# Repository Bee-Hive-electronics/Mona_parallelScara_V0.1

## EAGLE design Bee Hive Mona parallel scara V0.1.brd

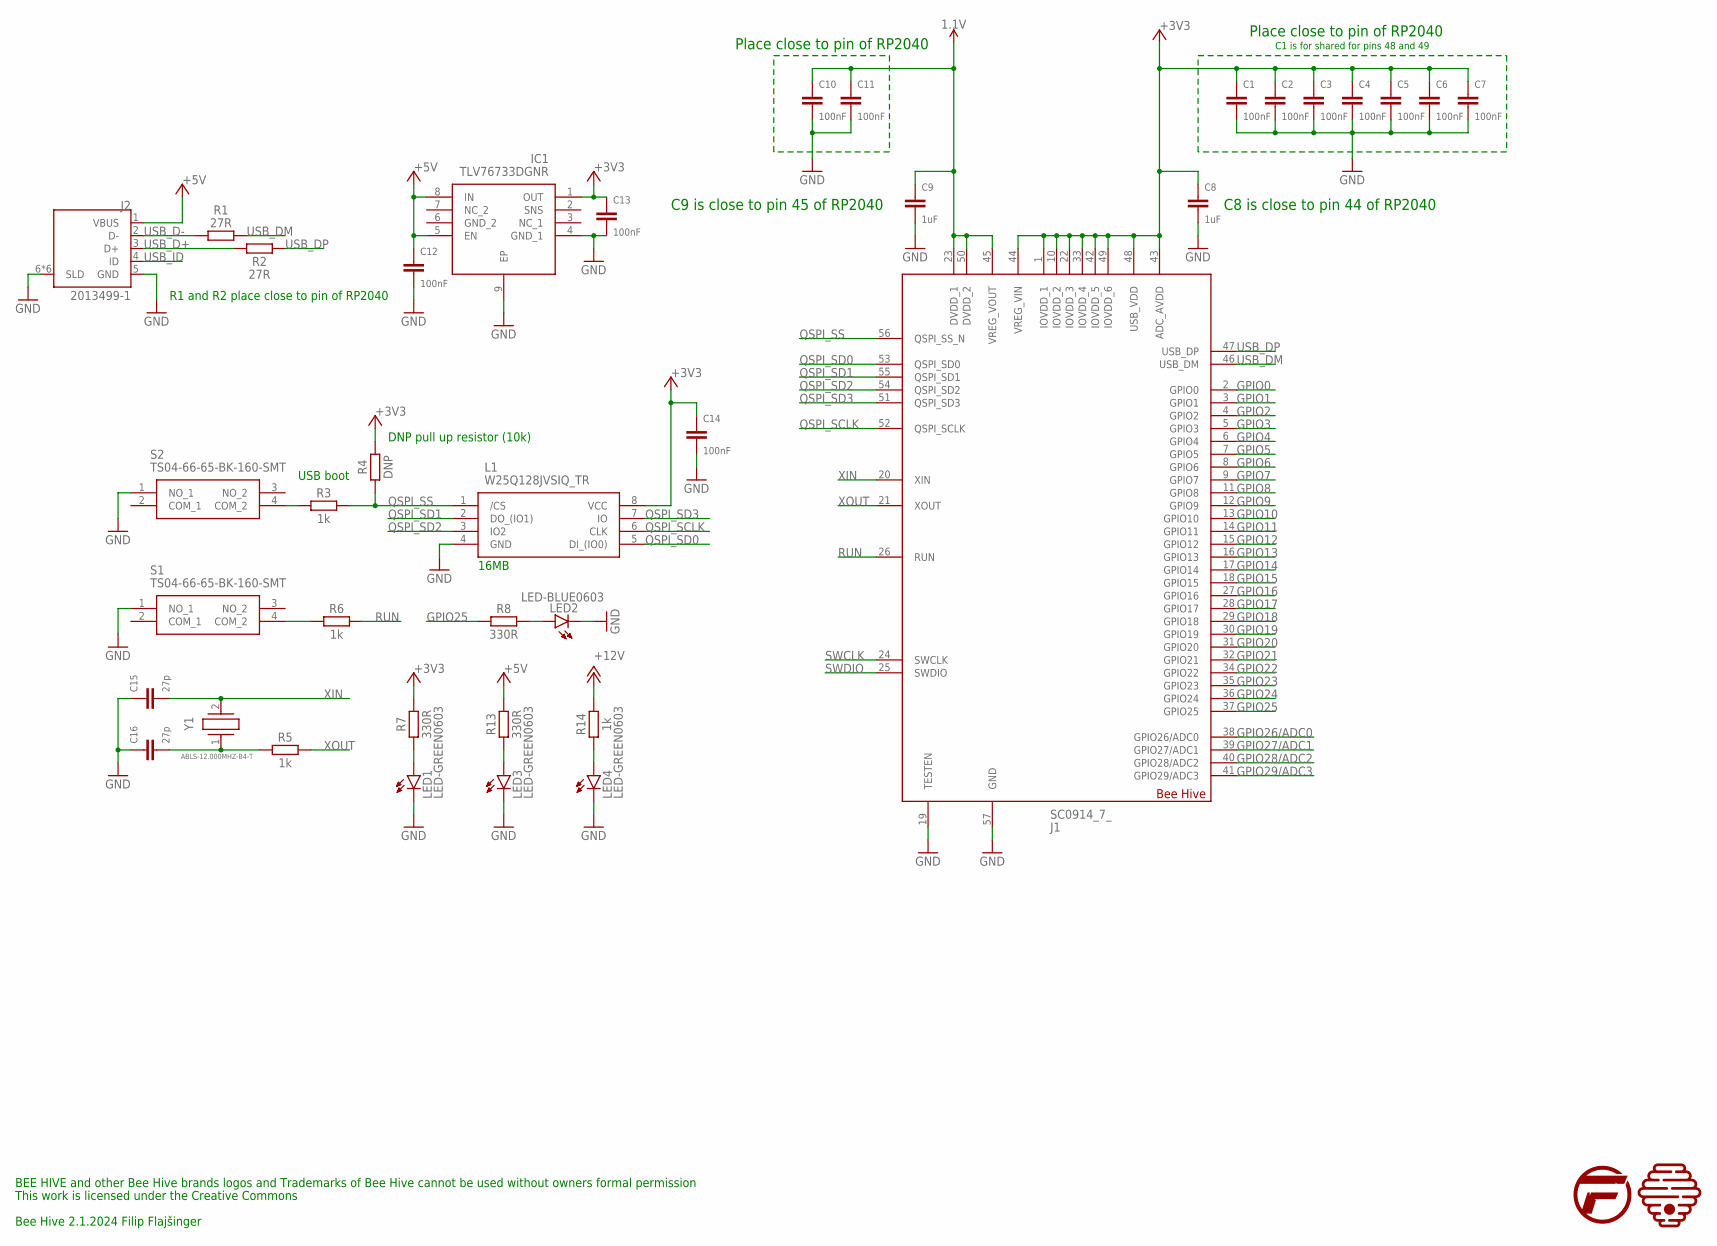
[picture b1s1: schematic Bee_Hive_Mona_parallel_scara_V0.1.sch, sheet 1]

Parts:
C1, C2, C3, C4, C5, C6, C7, C10, C11, C12, C13, C14: 100nF; CAPC1608X85
C8, C9: 1uF; CAPC1608X85
C15, C16: 27p; CAPC1608X85
IC1: TLV76733DGNR; SOP65P490X110-9N
J1: SC0914_7_; QFN40P700X700X90-57N
J2: 2013499-1; TE_2013499-1
L1: W25Q128JVSIQ_TR; SOIC127P780X195-8N
LED1, LED3, LED4: LED-GREEN0603; 0603-GREEN
LED2: LED-BLUE0603; 0603-BLUE
R1, R2: 27R; RESC1608X60
R3, R5, R6, R14: 1k; RESC1608X60
R4: DNP; RESC1608X60
R7, R8, R13: 330R; RESC1608X60
S1, S2: TS04-66-65-BK-160-SMT; TS046665BK160SMT
Y1: ABLS-12.000MHZ-B4-T; ABLS

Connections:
1.1V: C9.1, C10.1, C11.1, J1.23 (DVDD_1), J1.45 (VREG_VOUT), J1.50 (DVDD_2)
+3V3: C1.1, C2.1, C3.1, C4.1, C5.1, C6.1, C7.1, C8.1, C13.1, C14.1, IC1.1 (OUT), J1.1 (IOVDD_1), J1.10 (IOVDD_2), J1.22 (IOVDD_3), J1.33 (IOVDD_4), J1.42 (IOVDD_5), J1.43 (ADC_AVDD), J1.44 (VREG_VIN), J1.48 (USB_VDD), J1.49 (IOVDD_6), L1.8 (VCC), R4.2, R7.2; also elsewhere on the board
+5V: C12.1, IC1.5 (EN), IC1.8 (IN), J2.1 (VBUS), R13.2; also elsewhere on the board
+12V: R14.2; also elsewhere on the board
GND: C1.2, C2.2, C3.2, C4.2, C5.2, C6.2, C7.2, C8.2, C9.2, C10.2, C11.2, C12.2, C13.2, C14.2, C15.1, C16.1, IC1.4 (GND_1), IC1.9 (EP), J1.19 (TESTEN), J1.57 (GND), J2.5 (GND), J2.6 (SLD), J2.7 (SLD), J2.8 (SLD), J2.9 (SLD), J2.10 (SLD), J2.11 (SLD), L1.4 (GND), LED1.C, LED2.C, LED3.C, LED4.C, S1.1 (NO_1), S2.1 (NO_1); also elsewhere on the board
GPIO0: J1.2 (GPIO0); also elsewhere on the board
GPIO1: J1.3 (GPIO1); also elsewhere on the board
GPIO2: J1.4 (GPIO2); also elsewhere on the board
GPIO3: J1.5 (GPIO3); also elsewhere on the board
GPIO4: J1.6 (GPIO4); also elsewhere on the board
GPIO5: J1.7 (GPIO5); also elsewhere on the board
GPIO6: J1.8 (GPIO6); also elsewhere on the board
GPIO7: J1.9 (GPIO7); also elsewhere on the board
GPIO8: J1.11 (GPIO8); also elsewhere on the board
GPIO9: J1.12 (GPIO9); also elsewhere on the board
GPIO10: J1.13 (GPIO10); also elsewhere on the board
GPIO11: J1.14 (GPIO11); also elsewhere on the board
GPIO12: J1.15 (GPIO12); also elsewhere on the board
GPIO13: J1.16 (GPIO13); also elsewhere on the board
GPIO14: J1.17 (GPIO14); also elsewhere on the board
GPIO15: J1.18 (GPIO15); also elsewhere on the board
GPIO16: J1.27 (GPIO16); also elsewhere on the board
GPIO17: J1.28 (GPIO17); also elsewhere on the board
GPIO18: J1.29 (GPIO18); also elsewhere on the board
GPIO19: J1.30 (GPIO19); also elsewhere on the board
GPIO20: J1.31 (GPIO20); also elsewhere on the board
GPIO21: J1.32 (GPIO21); also elsewhere on the board
GPIO22: J1.34 (GPIO22); also elsewhere on the board
GPIO23: J1.35 (GPIO23); also elsewhere on the board
GPIO24: J1.36 (GPIO24); also elsewhere on the board
GPIO25: J1.37 (GPIO25), R8.2; also elsewhere on the board
GPIO26/ADC0: J1.38 (GPIO26/ADC0); also elsewhere on the board
GPIO27/ADC1: J1.39 (GPIO27/ADC1); also elsewhere on the board
GPIO28/ADC2: J1.40 (GPIO28/ADC2); also elsewhere on the board
GPIO29/ADC3: J1.41 (GPIO29/ADC3); also elsewhere on the board
unnamed: R3.1, S2.4 (COM_2)
unnamed: R6.1, S1.4 (COM_2)
unnamed: C16.2, R5.1, Y1.1
unnamed: LED2.A, R8.1
unnamed: LED1.A, R7.1
unnamed: LED3.A, R13.1
unnamed: LED4.A, R14.1
QSPI_SCLK: J1.52 (QSPI_SCLK), L1.6 (CLK)
QSPI_SD0: J1.53 (QSPI_SD0), L1.5 (DI_(IO0))
QSPI_SD1: J1.55 (QSPI_SD1), L1.2 (DO_(IO1))
QSPI_SD2: J1.54 (QSPI_SD2), L1.3 (IO2)
QSPI_SD3: J1.51 (QSPI_SD3), L1.7 (IO)
QSPI_SS: J1.56 (QSPI_SS_N), L1.1 (/CS), R3.2, R4.1
RUN: J1.26 (RUN), R6.2
SWCLK: J1.24 (SWCLK)
SWDIO: J1.25 (SWDIO)
USB_D+: J2.3 (D+), R2.1
USB_D-: J2.2 (D-), R1.1
USB_DM: J1.46 (USB_DM), R1.2
USB_DP: J1.47 (USB_DP), R2.2
USB_ID: J2.4 (ID)
XIN: C15.2, J1.20 (XIN), Y1.2
XOUT: J1.21 (XOUT), R5.2

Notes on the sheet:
C8 is close to pin 44 of RP2040
Place close to pin of RP2040
C9 is close to pin 45 of RP2040
C1 is for shared for pins 48 and 49
R1 and R2 place close to pin of RP2040
USB boot
DNP pull up resistor (10k)
16MB
This work is licensed under the Creative Commons
BEE HIVE and other Bee Hive brands logos and Trademarks of Bee Hive cannot be used without owners formal permission
Bee Hive 2.1.2024 Filip Flajšinger

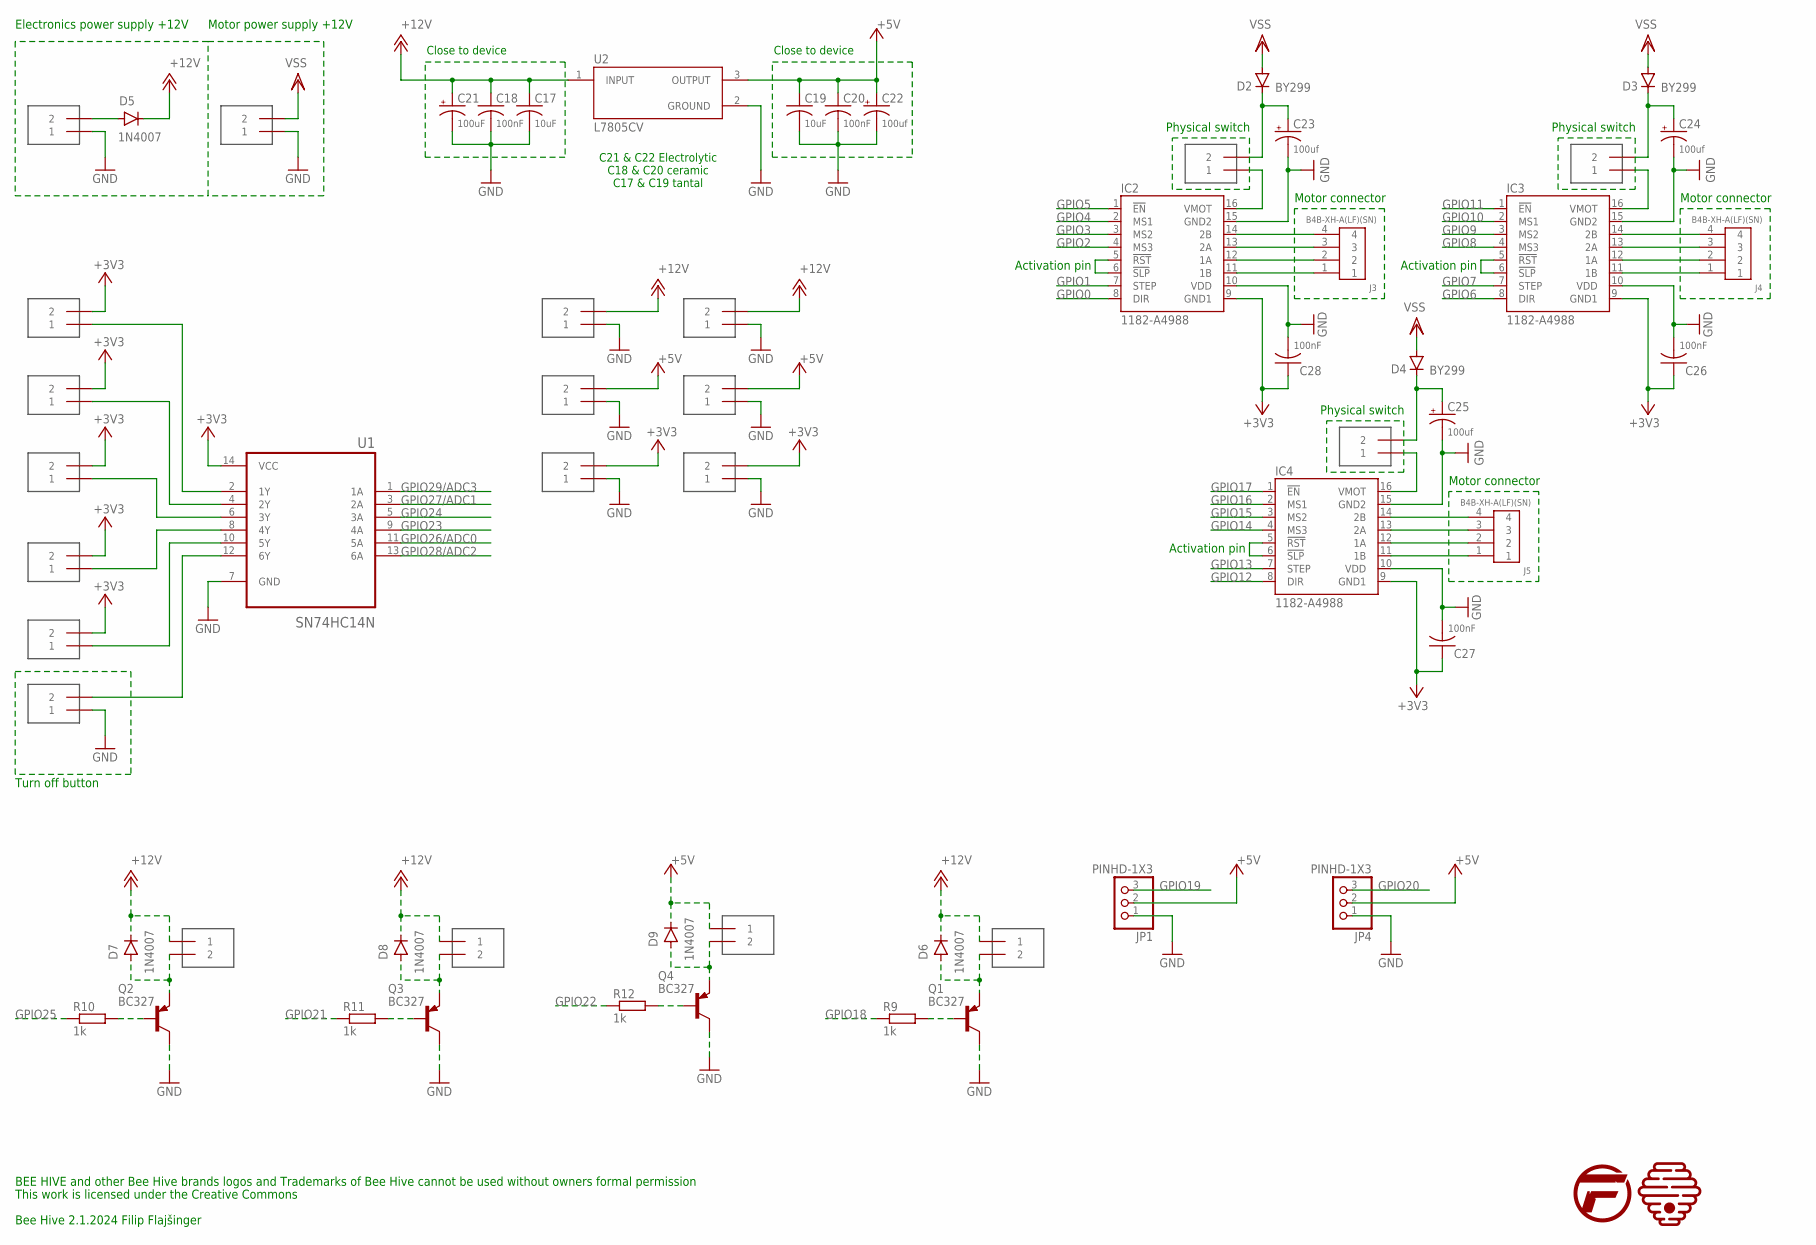
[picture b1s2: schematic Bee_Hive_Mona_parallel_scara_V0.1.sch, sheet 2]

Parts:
C17, C19: 10uF; C025-024X044
C18, C20, C26, C27, C28: 100nF; C025-024X044
C21: 100uF; E1,8-4
C22, C23, C24, C25: 100uf; E1,8-4
D2, D3, D4: BY299; DO15-12
D5, D6, D7, D8, D9: 1N4007; DO-41
IC2, IC3, IC4: 1182-A4988; A4988
J3, J4, J5: B4B-XH-A(LF)(SN)
JP1, JP4: PINHD-1X3; 1X03
Q1, Q2, Q3, Q4: BC327; TO92
R9, R10, R11, R12: 1k; 0204/7
U1: SN74HC14N; DIP794W45P254L1969H508Q14
U2: L7805CV; TO255P1040X460X1968-3
U$1, U$2, U$3, U$4, U$5, U$6, U$7, U$8, U$9, U$10, U$11, U$12, U$15, U$16, U$17, U$18, U$19, U$20, U$21, U$22, U$23: TERMINAL_2P; KF301-2P

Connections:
+3V3: C26.1, C27.1, C28.1, IC2.9 (GND1), IC3.9 (GND1), IC4.9 (GND1), U1.14 (VCC), U$12.2, U$17.2, U$18.2, U$19.2, U$20.2, U$21.2, U$23.2; also elsewhere on the board
+5V: C19.1, C20.1, C22.+, D9.C, JP1.2, JP4.2, U2.3 (OUTPUT), U$9.1, U$11.2, U$16.2; also elsewhere on the board
+12V: C17.1, C18.1, C21.+, D5.C, D6.C, D7.C, D8.C, U2.1 (INPUT), U$6.1, U$7.1, U$8.1, U$10.2, U$15.2; also elsewhere on the board
GND: C17.2, C18.2, C19.2, C20.2, C21.-, C22.-, C23.-, C24.-, C25.-, C26.2, C27.2, C28.2, IC2.10 (VDD), IC2.15 (GND2), IC3.10 (VDD), IC3.15 (GND2), IC4.10 (VDD), IC4.15 (GND2), JP1.1, JP4.1, Q1.3 (C), Q2.3 (C), Q3.3 (C), Q4.3 (C), U1.7 (GND), U2.2 (GROUND), U$4.1, U$5.1, U$10.1, U$11.1, U$12.1, U$15.1, U$16.1, U$17.1, U$22.1; also elsewhere on the board
GPIO0: IC2.8 (DIR); also elsewhere on the board
GPIO1: IC2.7 (STEP); also elsewhere on the board
GPIO2: IC2.4 (MS3); also elsewhere on the board
GPIO3: IC2.3 (MS2); also elsewhere on the board
GPIO4: IC2.2 (MS1); also elsewhere on the board
GPIO5: IC2.1 (!EN); also elsewhere on the board
GPIO6: IC3.8 (DIR); also elsewhere on the board
GPIO7: IC3.7 (STEP); also elsewhere on the board
GPIO8: IC3.4 (MS3); also elsewhere on the board
GPIO9: IC3.3 (MS2); also elsewhere on the board
GPIO10: IC3.2 (MS1); also elsewhere on the board
GPIO11: IC3.1 (!EN); also elsewhere on the board
GPIO12: IC4.8 (DIR); also elsewhere on the board
GPIO13: IC4.7 (STEP); also elsewhere on the board
GPIO14: IC4.4 (MS3); also elsewhere on the board
GPIO15: IC4.3 (MS2); also elsewhere on the board
GPIO16: IC4.2 (MS1); also elsewhere on the board
GPIO17: IC4.1 (!EN); also elsewhere on the board
GPIO18: R9.1; also elsewhere on the board
GPIO19: JP1.3; also elsewhere on the board
GPIO20: JP4.3; also elsewhere on the board
GPIO21: R11.1; also elsewhere on the board
GPIO22: R12.1; also elsewhere on the board
GPIO23: U1.9 (4A); also elsewhere on the board
GPIO24: U1.5 (3A); also elsewhere on the board
GPIO25: R10.1; also elsewhere on the board
GPIO26/ADC0: U1.11 (5A); also elsewhere on the board
GPIO27/ADC1: U1.3 (2A); also elsewhere on the board
GPIO28/ADC2: U1.13 (6A); also elsewhere on the board
GPIO29/ADC3: U1.1 (1A); also elsewhere on the board
unnamed: D5.A, U$4.2
unnamed: IC2.11 (1B), J3.1
unnamed: IC2.12 (1A), J3.2
unnamed: IC2.13 (2A), J3.3
unnamed: IC2.14 (2B), J3.4
unnamed: IC2.5 (!RST), IC2.6 (!SLP)
unnamed: IC2.16 (VMOT), U$1.1
unnamed: IC3.16 (VMOT), U$2.1
unnamed: IC4.16 (VMOT), U$3.1
unnamed: IC3.11 (1B), J4.1
unnamed: IC3.12 (1A), J4.2
unnamed: IC3.13 (2A), J4.3
unnamed: IC3.14 (2B), J4.4
unnamed: IC3.5 (!RST), IC3.6 (!SLP)
unnamed: C23.+, D2.C, U$1.2
unnamed: C24.+, D3.C, U$2.2
unnamed: C25.+, D4.C, U$3.2
unnamed: IC4.11 (1B), J5.1
unnamed: IC4.12 (1A), J5.2
unnamed: IC4.13 (2A), J5.3
unnamed: IC4.14 (2B), J5.4
unnamed: IC4.5 (!RST), IC4.6 (!SLP)
unnamed: D6.A, Q1.1 (E), U$6.2
unnamed: Q1.2 (B), R9.2
unnamed: D7.A, Q2.1 (E), U$7.2
unnamed: Q2.2 (B), R10.2
unnamed: D8.A, Q3.1 (E), U$8.2
unnamed: Q3.2 (B), R11.2
unnamed: D9.A, Q4.1 (E), U$9.2
unnamed: Q4.2 (B), R12.2
unnamed: U1.8 (4Y), U$21.1
unnamed: U1.6 (3Y), U$19.1
unnamed: U1.4 (2Y), U$18.1
unnamed: U1.2 (1Y), U$23.1
unnamed: U1.10 (5Y), U$20.1
unnamed: U1.12 (6Y), U$22.2
VSS: D2.A, D3.A, D4.A, U$5.2

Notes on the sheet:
Close to device
Physical switch
Motor connector
Activation pin
C21 & C22 Electrolytic C18 & C20 ceramic C17 & C19 tantal
Motor power supply +12V
Electronics power supply +12V
Turn off button
This work is licensed under the Creative Commons
BEE HIVE and other Bee Hive brands logos and Trademarks of Bee Hive cannot be used without owners formal permission
Bee Hive 2.1.2024 Filip Flajšinger

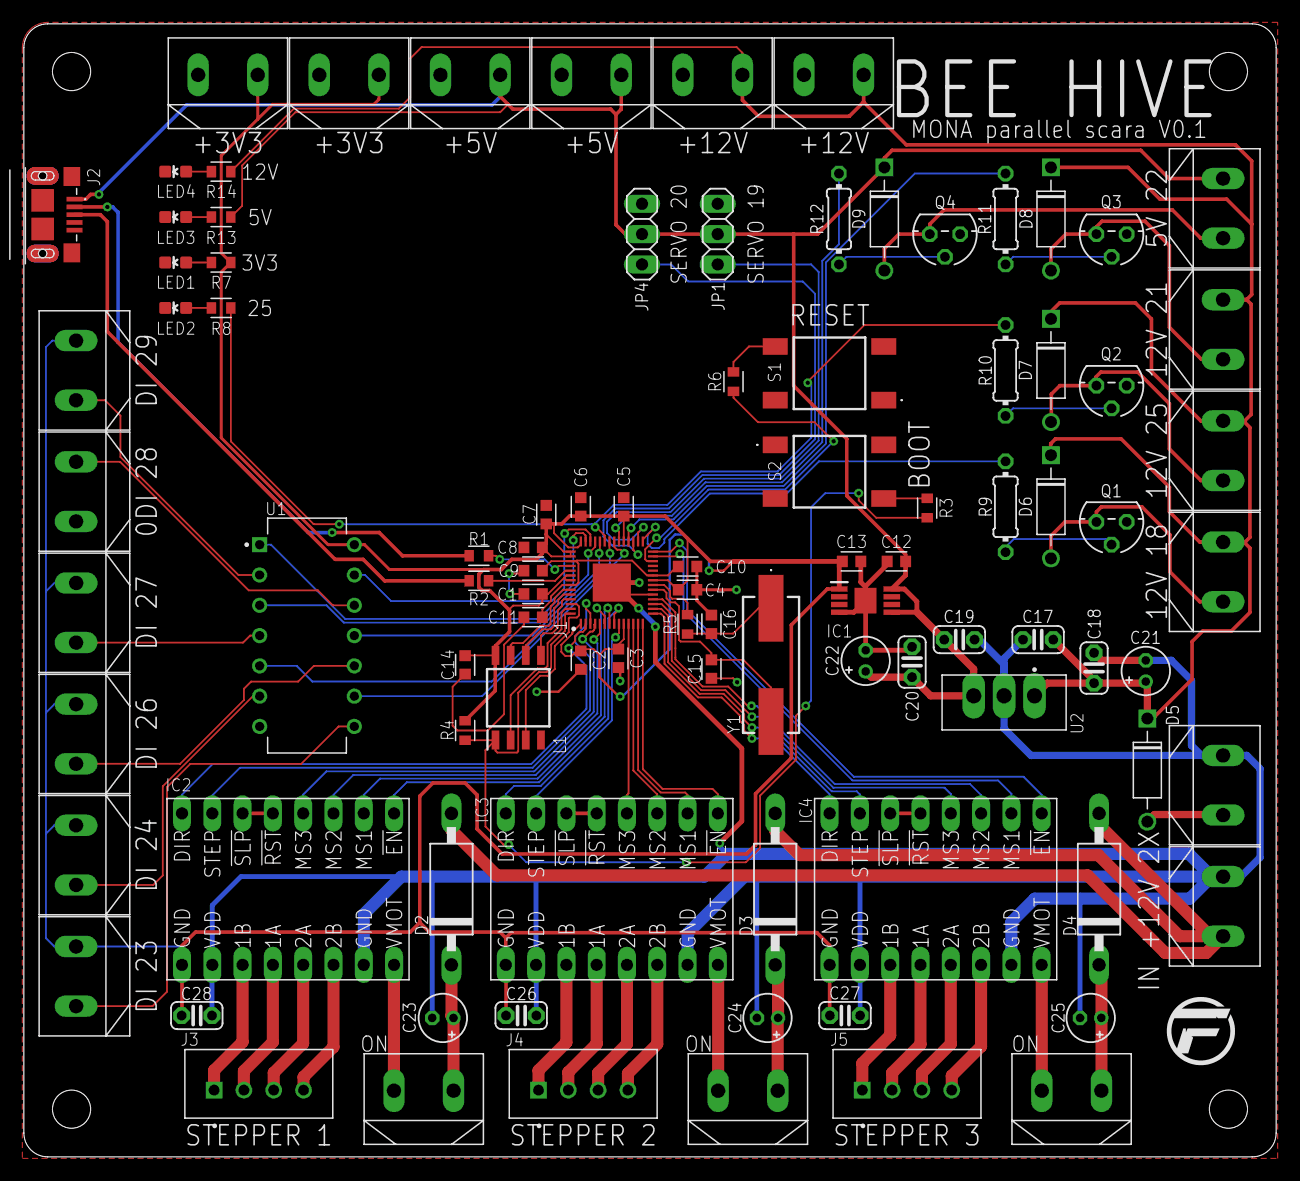
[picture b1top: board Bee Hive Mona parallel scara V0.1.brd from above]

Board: 2 copper layers, 105.0 x 95.0 mm, 96 parts (0 on the bottom side), 92 nets.

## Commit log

2024-05-01 MONA: Add schematics, board, fusion, PDF, PNG

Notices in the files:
parts and their libraries:
SparkFun-PowerSymbols: Licensing: Creative Commons ShareAlike 4.0 International - https://creativecommons.org/licenses/by-sa/4.0
